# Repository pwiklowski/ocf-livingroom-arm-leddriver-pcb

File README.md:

# What is it ?

Repository contains schematic + pcb for 3 channel PWM led driver (can be extended up to 6 channels). STM32F030 was used as PWM generator as it is (probably) the cheapest cortex m0 uC. 

# Why I haven't used one of dedicated chips such as WS2801 ?

I've tried but they are not as good as you may think. Their PWM frequency is to high. Cheap LED bulbs are freaking out (random blinking etc.) when you will power it with 2.5[kHz] PWM. Custom driver is much more flexible and freqency can be set to much lower value (~400Hz). Another advantage of lower frequency is driving mosfets directly from uC - no speed boosters needed. It can handle up to 60-70[W] of load per channel(no heat sink).

# Part list

- 3x IRLR7821PBF (schematic contains different part number)
- 1x STM32F030
- 2x 10k resistor
- 1x 10uF capcitor (TODO: add 100nF for uC)
- some connectors

# How to open it ?

I'm using Eeagle 7 (https://cadsoft.io/). It is good, free and what is the most important it can be installed on GNU/Linux. 

# Images
## Schematic

## PCB

## Prototype

## Manutactured PCB

## Manufactured PCB with mounted elements
TODO

# License
Apache License, Version 2.0

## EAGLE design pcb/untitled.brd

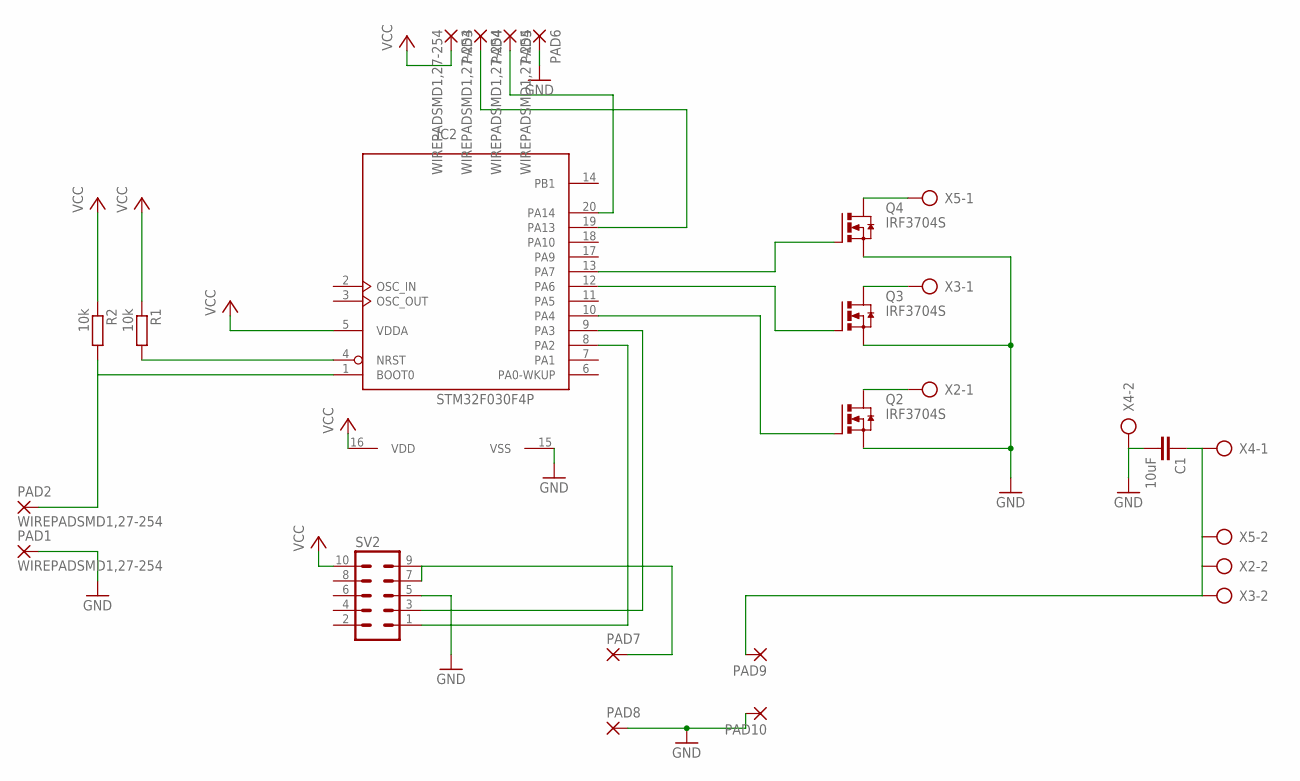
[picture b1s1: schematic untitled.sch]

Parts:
C1: 10uF; C025-050X050
IC2: STM32F030F4P; TSSOP20-I
PAD1, PAD2, PAD3, PAD4, PAD5, PAD6: WIREPADSMD1,27-254; SMD1,27-2,54
PAD7, PAD8, PAD9, PAD10: SMD5; SMD2,54-5,08
Q2, Q3, Q4: IRF3704S; D2PACK
R1, R2: 10k; R1206
SV2: MA05-2
X2, X3, X4, X5: AK500/2

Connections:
GND: C1.2, IC2.15 (VSS), PAD1.1, PAD6.1, PAD8.1, PAD10.1, Q2.3 (S), Q3.3 (S), Q4.3 (S), SV2.5, X4.2
unnamed: PAD7.1, SV2.7, SV2.9
unnamed: IC2.8 (PA2), SV2.1
unnamed: C1.1, PAD9.1, X2.2, X3.2, X4.1, X5.2
unnamed: IC2.9 (PA3), SV2.3
unnamed: Q4.2 (D), X5.1
unnamed: IC2.20 (PA14), PAD5.1
unnamed: IC2.13 (PA7), Q4.1 (G)
unnamed: IC2.10 (PA4), Q2.1 (G)
unnamed: IC2.12 (PA6), Q3.1 (G)
unnamed: IC2.19 (PA13), PAD4.1
unnamed: Q2.2 (D), X2.1
unnamed: IC2.4 (NRST), R1.2
unnamed: IC2.1 (BOOT0), PAD2.1, R2.2
unnamed: Q3.2 (D), X3.1
VCC: IC2.5 (VDDA), IC2.16 (VDD), PAD3.1, R1.1, R2.1, SV2.10

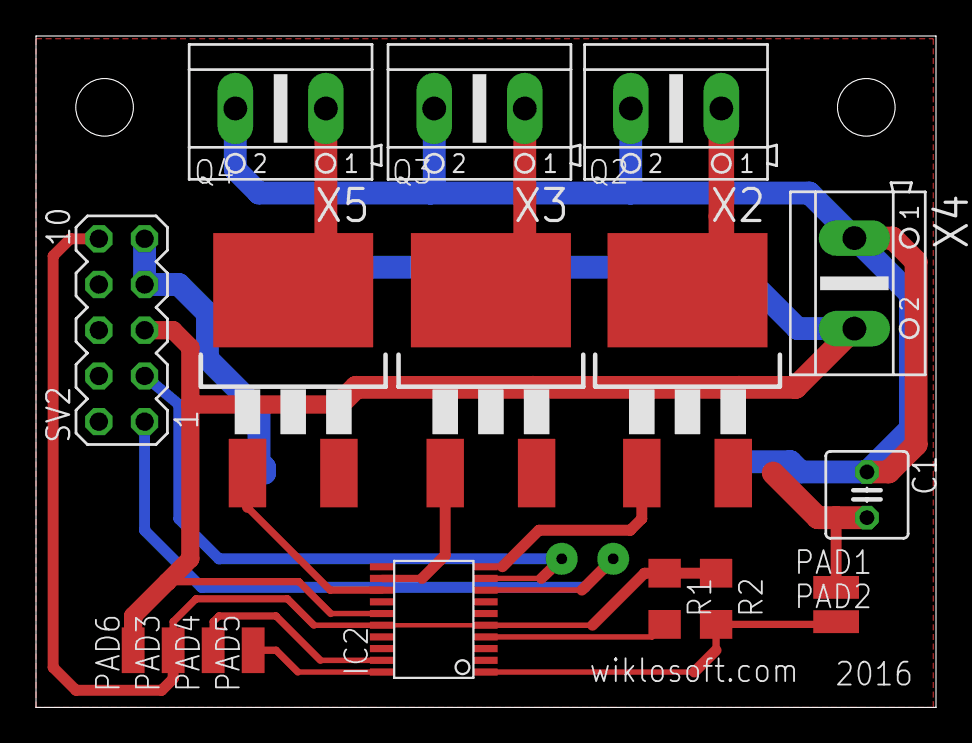
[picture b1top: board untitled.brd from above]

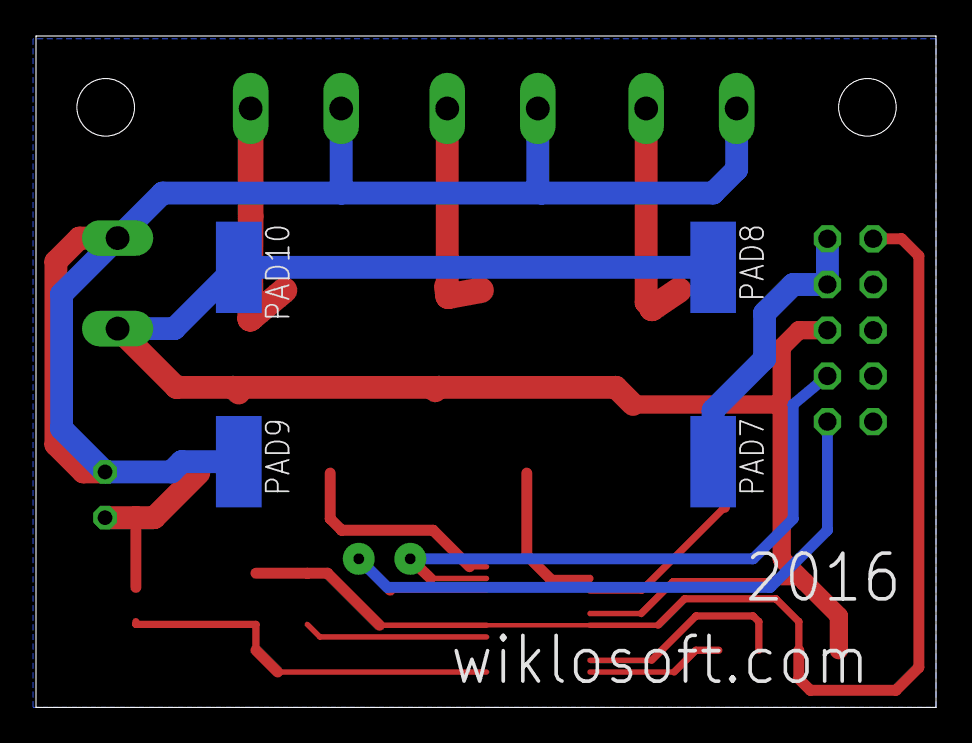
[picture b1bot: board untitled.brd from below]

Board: 2 copper layers, 50.0 x 37.3 mm, 22 parts (4 on the bottom side), 16 nets.

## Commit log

2016-11-02 Add eagle files
2016-11-02 Add readme
